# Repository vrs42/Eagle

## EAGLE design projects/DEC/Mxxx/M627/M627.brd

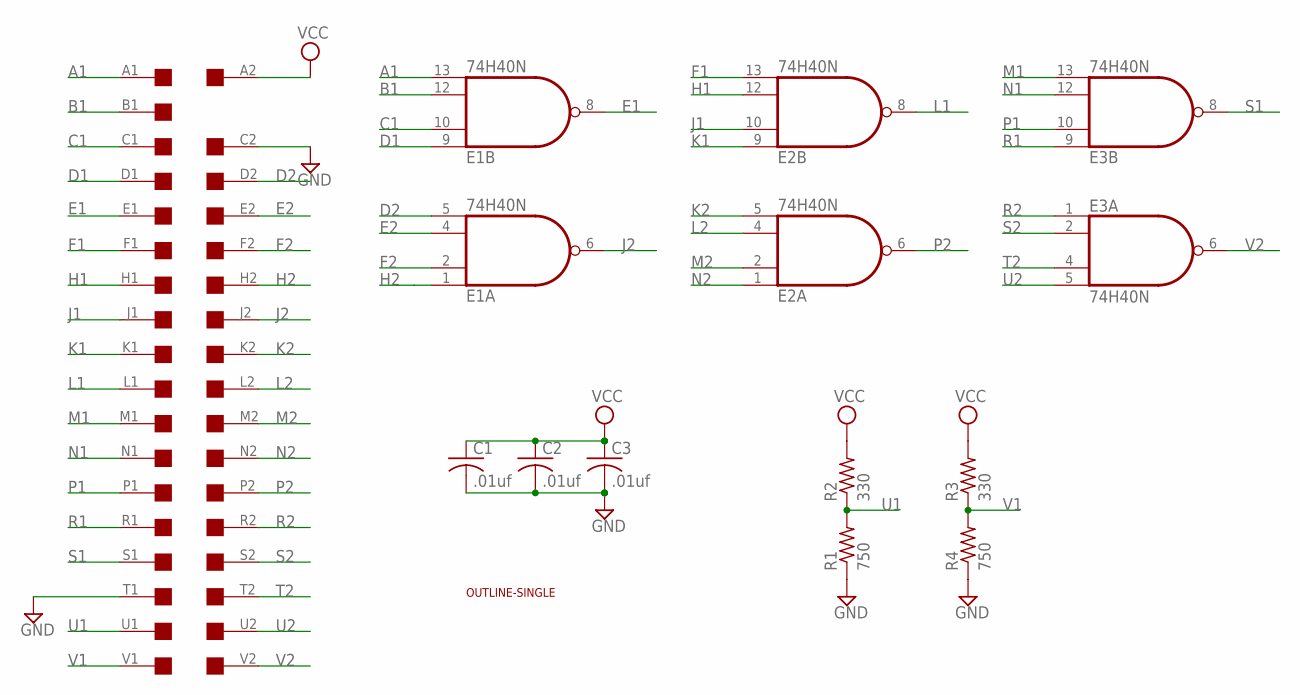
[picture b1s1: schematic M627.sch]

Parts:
C1, C2, C3: .01uf; C050-025X075
E1, E2, E3: 74H40N; DIL14
R1, R4: 750; 0207/10
R2, R3: 330; 0207/10
U$1: OUTLINE-SINGLE; SINGLE
U$2: SINGLE; EDGE-CON2

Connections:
A1: E1.13 (I3), U$2.A1
B1: E1.12 (I2), U$2.B1
C1: E1.10 (I1), U$2.C1
D1: E1.9 (I0), U$2.D1
D2: E1.5 (I3), U$2.D2
E1: E1.8 (O), U$2.E1
E2: E1.4 (I2), U$2.E2
F1: E2.13 (I3), U$2.F1
F2: E1.2 (I1), U$2.F2
GND: C1.2, C2.2, C3.2, E1.7 (GND), E2.7 (GND), E3.7 (GND), R1.1, R4.1, U$2.C2, U$2.T1
H1: E2.12 (I2), U$2.H1
H2: E1.1 (I0), U$2.H2
J1: E2.10 (I1), U$2.J1
J2: E1.6 (O), U$2.J2
K1: E2.9 (I0), U$2.K1
K2: E2.5 (I3), U$2.K2
L1: E2.8 (O), U$2.L1
L2: E2.4 (I2), U$2.L2
M1: E3.13 (I3), U$2.M1
M2: E2.2 (I1), U$2.M2
N1: E3.12 (I2), U$2.N1
N2: E2.1 (I0), U$2.N2
P1: E3.10 (I1), U$2.P1
P2: E2.6 (O), U$2.P2
R1: E3.9 (I0), U$2.R1
R2: E3.1 (I0), U$2.R2
S1: E3.8 (O), U$2.S1
S2: E3.2 (I1), U$2.S2
T2: E3.4 (I2), U$2.T2
U1: R1.2, R2.1, U$2.U1
U2: E3.5 (I3), U$2.U2
V1: R3.1, R4.2, U$2.V1
V2: E3.6 (O), U$2.V2
VCC: C1.1, C2.1, C3.1, E1.14 (VCC), E2.14 (VCC), E3.14 (VCC), R2.2, R3.2, U$2.A2

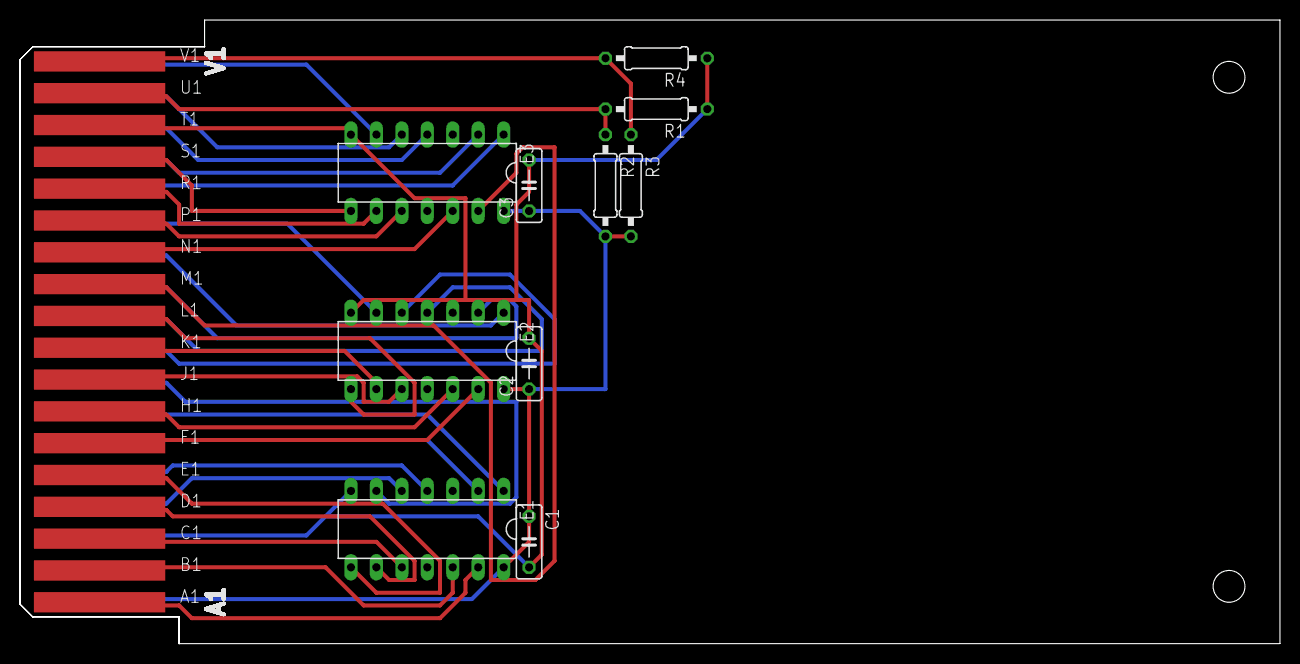
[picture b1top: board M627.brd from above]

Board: 2 copper layers, 125.7 x 62.2 mm, 12 parts (0 on the bottom side), 34 nets.

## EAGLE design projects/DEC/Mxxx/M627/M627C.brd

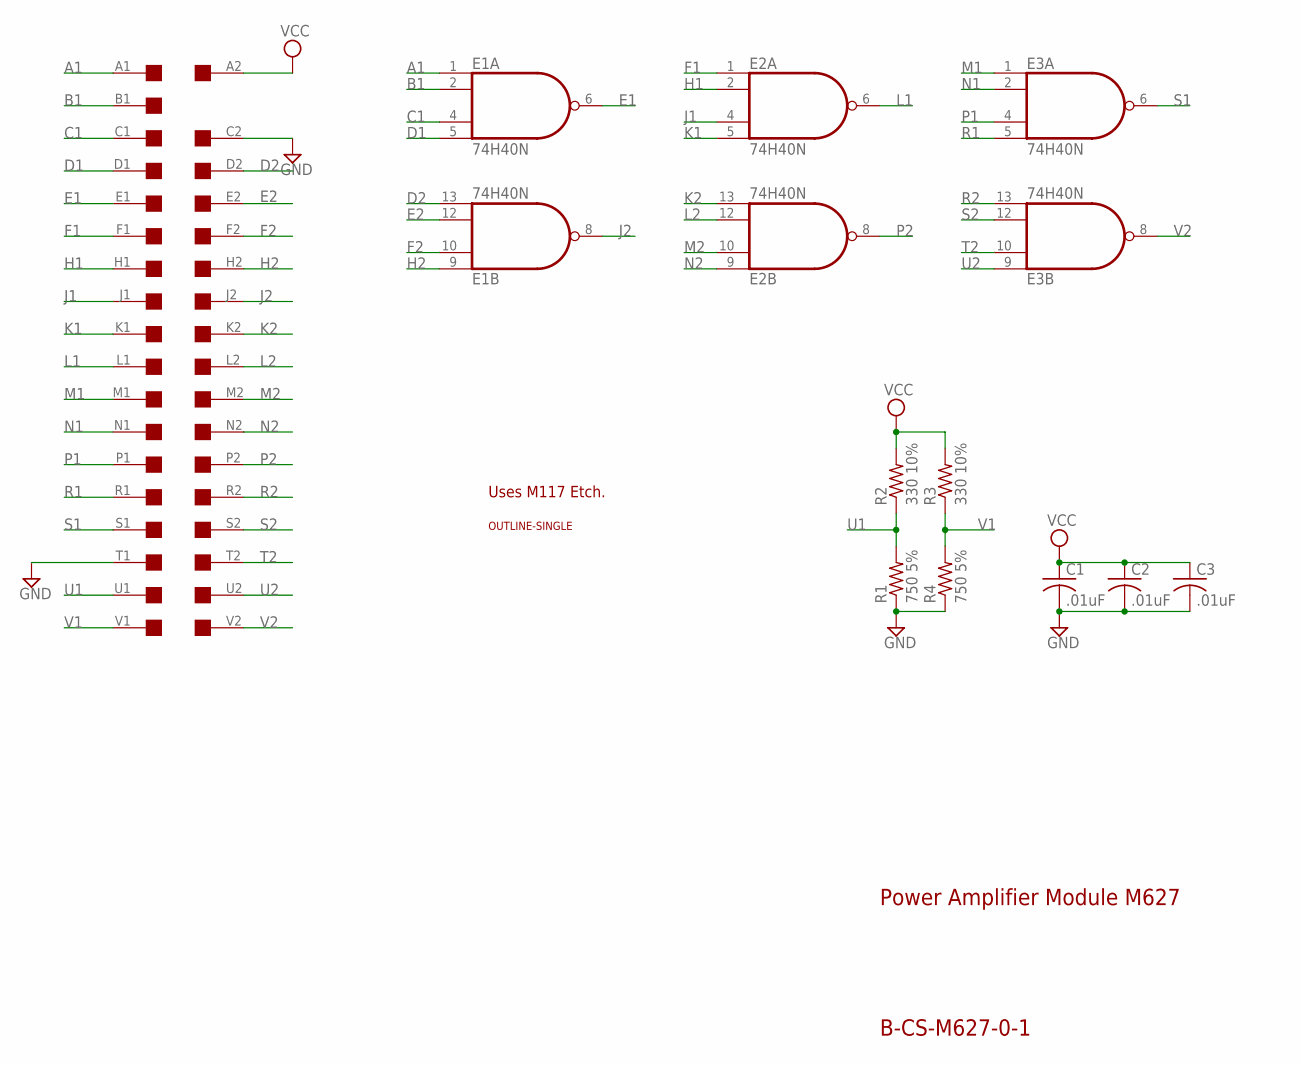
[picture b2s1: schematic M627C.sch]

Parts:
C1, C2, C3: .01uF; C050-025X075
E1, E2, E3: 74H40N; DIL14
R1, R4: 750 5%; 0207/10
R2, R3: 330 10%; 0207/10
U$1: SINGLE; EDGE-CON2
U$4: OUTLINE-SINGLE; SINGLE

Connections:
A1: E1.1 (I0), U$1.A1
B1: E1.2 (I1), U$1.B1
C1: E1.4 (I2), U$1.C1
D1: E1.5 (I3), U$1.D1
D2: E1.13 (I3), U$1.D2
E1: E1.6 (O), U$1.E1
E2: E1.12 (I2), U$1.E2
F1: E2.1 (I0), U$1.F1
F2: E1.10 (I1), U$1.F2
GND: C1.2, C2.2, C3.2, E1.7 (GND), E2.7 (GND), E3.7 (GND), R1.1, R4.1, U$1.C2, U$1.T1
H1: E2.2 (I1), U$1.H1
H2: E1.9 (I0), U$1.H2
J1: E2.4 (I2), U$1.J1
J2: E1.8 (O), U$1.J2
K1: E2.5 (I3), U$1.K1
K2: E2.13 (I3), U$1.K2
L1: E2.6 (O), U$1.L1
L2: E2.12 (I2), U$1.L2
M1: E3.1 (I0), U$1.M1
M2: E2.10 (I1), U$1.M2
N1: E3.2 (I1), U$1.N1
N2: E2.9 (I0), U$1.N2
P1: E3.4 (I2), U$1.P1
P2: E2.8 (O), U$1.P2
R1: E3.5 (I3), U$1.R1
R2: E3.13 (I3), U$1.R2
S1: E3.6 (O), U$1.S1
S2: E3.12 (I2), U$1.S2
T2: E3.10 (I1), U$1.T2
U1: R1.2, R2.1, U$1.U1
U2: E3.9 (I0), U$1.U2
V1: R3.1, R4.2, U$1.V1
V2: E3.8 (O), U$1.V2
VCC: C1.1, C2.1, C3.1, E1.14 (VCC), E2.14 (VCC), E3.14 (VCC), R2.2, R3.2, U$1.A2

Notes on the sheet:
Power Amplifier Module M627
B-CS-M627-0-1
Uses M117 Etch.

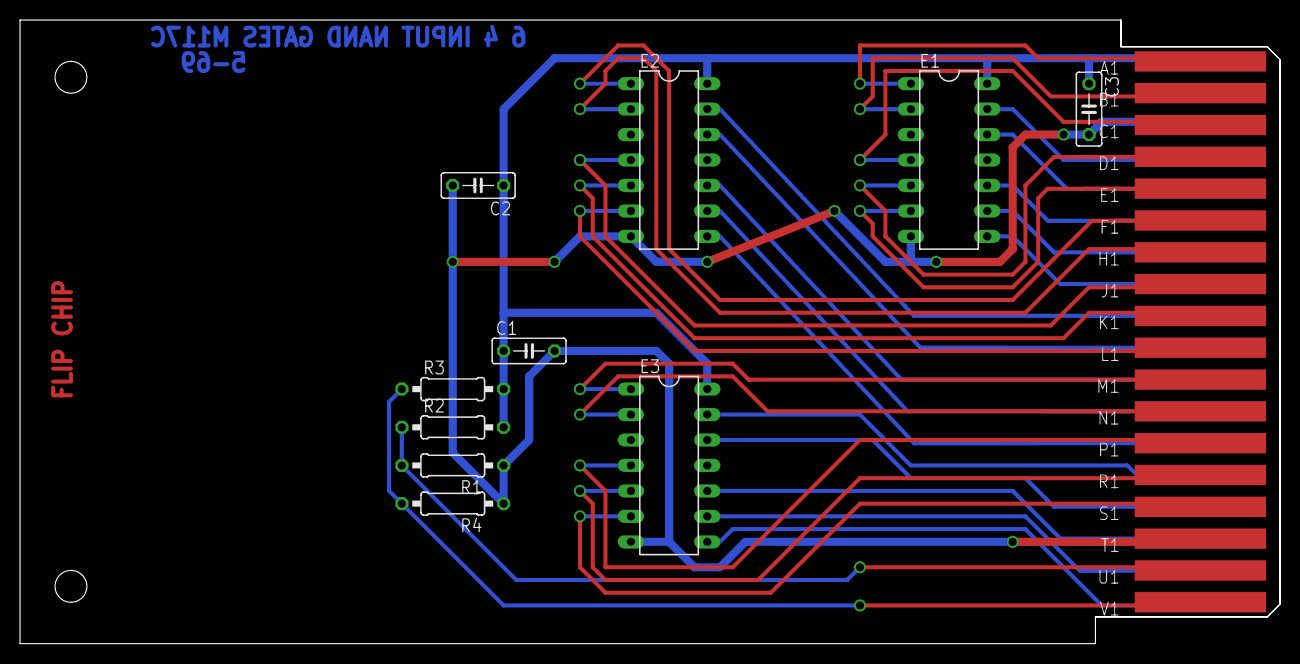
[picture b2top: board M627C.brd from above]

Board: 2 copper layers, 125.7 x 62.2 mm, 12 parts (0 on the bottom side), 34 nets.

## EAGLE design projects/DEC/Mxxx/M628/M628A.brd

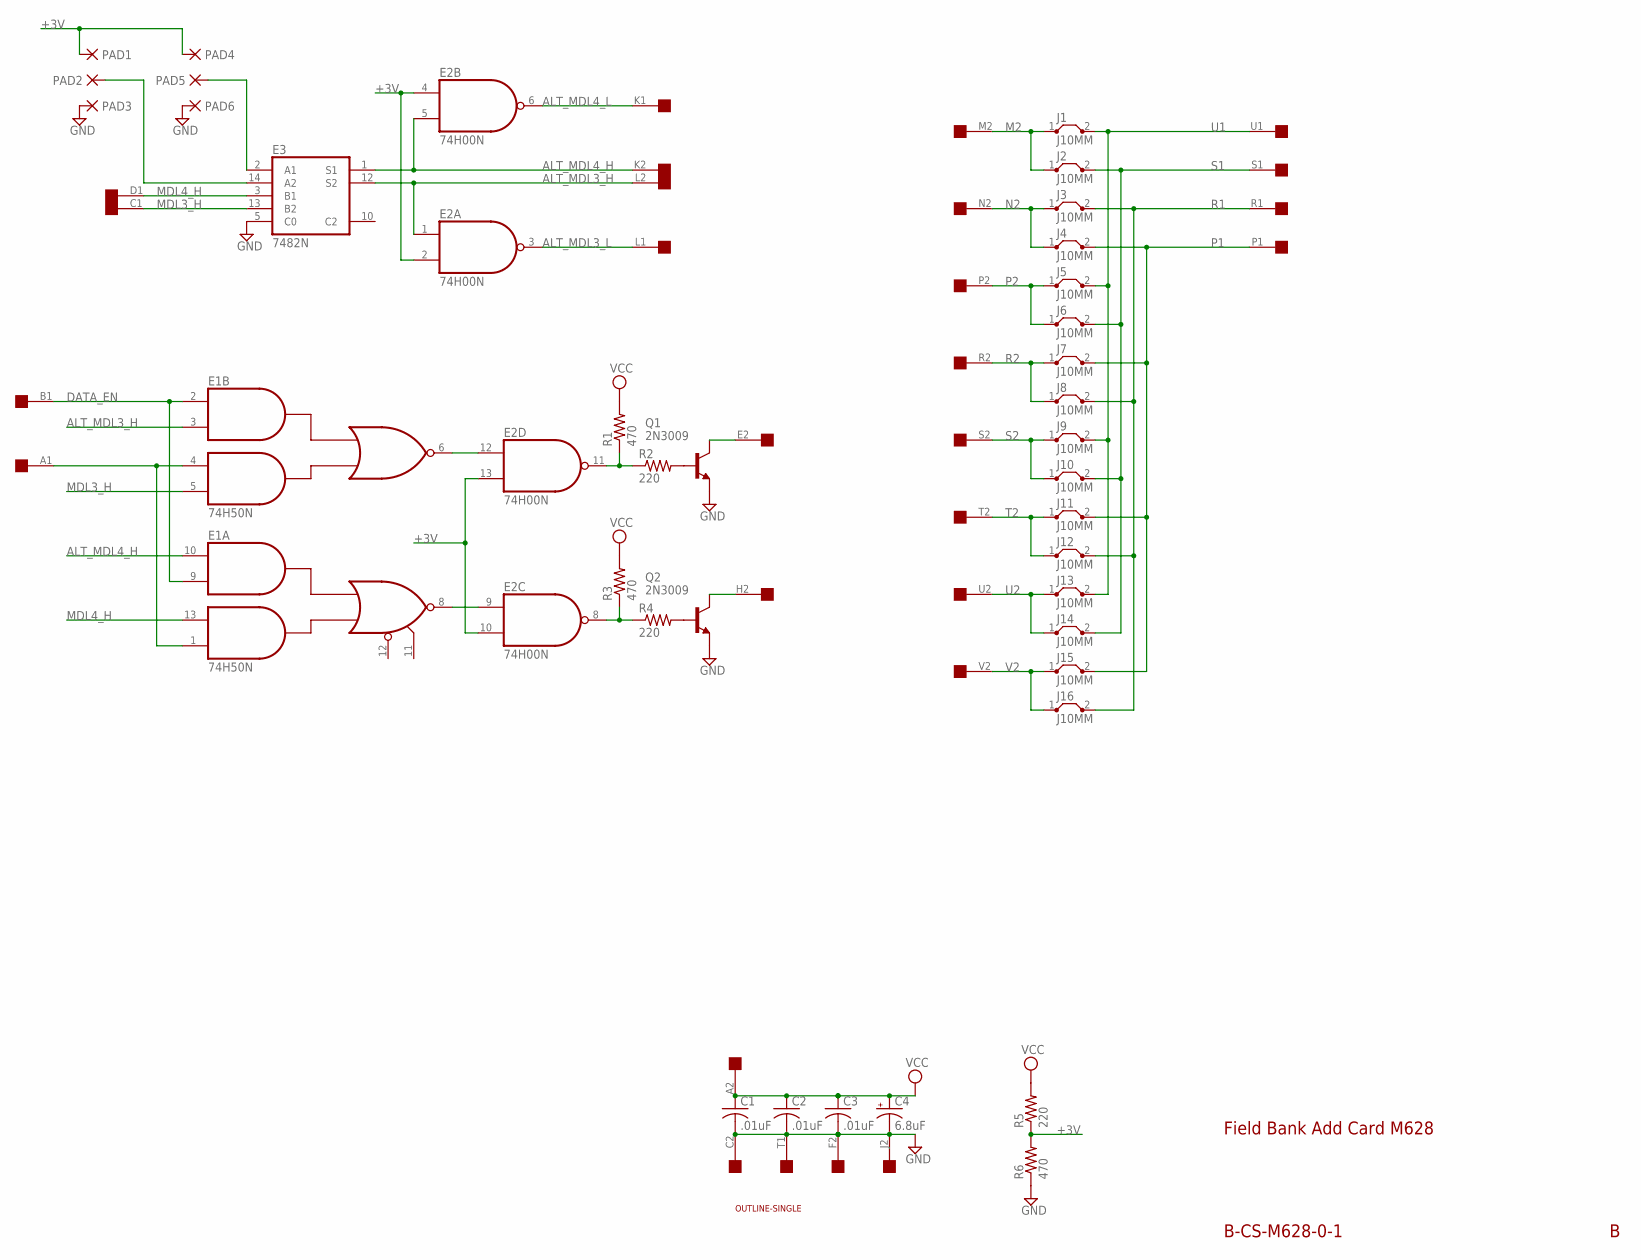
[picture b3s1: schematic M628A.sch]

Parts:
C1, C2, C3: .01uF; C050-025X075
C4: 6.8uF; E12-8
E1: 74H50N; DIL14
E2: 74H00N; DIL14
E3: 7482N; DIL14
J1, J2, J3, J4, J5, J6, J7, J8, J9, J10, J11, J12, J13, J14, J15, J16: J10MM; 10
PAD1, PAD2, PAD3, PAD4, PAD5, PAD6: PAD-0420; 0420
Q1, Q2: 2N3009; TO5
R1, R3, R6: 470; 0207/10
R2, R4, R5: 220; 0207/10
U$1: OUTLINE-SINGLE; SINGLE
U$2: SINGLE; EDGE-CON2

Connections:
+3V: E2.2 (I1), E2.4 (I0), E2.10 (I1), E2.13 (I1), PAD1.P$1, PAD4.P$1, R5.1, R6.2
ALT_MDL3_H: E1.3 (I2), E2.1 (I0), E3.12 (S2), U$2.L2
ALT_MDL3_L: E2.3 (O), U$2.L1
ALT_MDL4_H: E1.10 (I1), E2.5 (I1), E3.1 (S1), U$2.K2
ALT_MDL4_L: E2.6 (O), U$2.K1
DATA_EN: E1.2 (I1), E1.9 (I2), U$2.B1
GND: C1.2, C2.2, C3.2, C4.-, E1.7 (GND), E2.7 (GND), E3.5 (C0), E3.11 (GND), PAD3.P$1, PAD6.P$1, Q1.1 (E), Q2.1 (E), R6.1, U$2.C2, U$2.F2, U$2.J2, U$2.T1
M2: J1.1, J2.1, U$2.M2
MDL3_H: E1.5 (I4), E3.13 (B2), U$2.C1
MDL4_H: E1.13 (I3), E3.3 (B1), U$2.D1
N2: J3.1, J4.1, U$2.N2
unnamed: E3.2 (A1), PAD5.P$1
unnamed: E3.14 (A2), PAD2.P$1
unnamed: E1.8 (O), E2.9 (I0)
unnamed: E1.1 (I4), E1.4 (I3), U$2.A1
unnamed: E1.6 (O), E2.12 (I0)
unnamed: E2.11 (O), R1.1, R2.1
unnamed: E2.8 (O), R3.1, R4.1
unnamed: Q1.2 (B), R2.2
unnamed: Q2.2 (B), R4.2
unnamed: Q1.3 (C), U$2.E2
unnamed: Q2.3 (C), U$2.H2
P1: J4.2, J7.2, J11.2, J15.2, U$2.P1
P2: J5.1, J6.1, U$2.P2
R1: J3.2, J8.2, J12.2, J16.2, U$2.R1
R2: J7.1, J8.1, U$2.R2
S1: J2.2, J6.2, J10.2, J14.2, U$2.S1
S2: J9.1, J10.1, U$2.S2
T2: J11.1, J12.1, U$2.T2
U1: J1.2, J5.2, J9.2, J13.2, U$2.U1
U2: J13.1, J14.1, U$2.U2
V2: J15.1, J16.1, U$2.V2
VCC: C1.1, C2.1, C3.1, C4.+, E1.14 (VCC), E2.14 (VCC), E3.4 (VCC), R1.2, R3.2, R5.2, U$2.A2

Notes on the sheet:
Field Bank Add Card M628
B-CS-M628-0-1

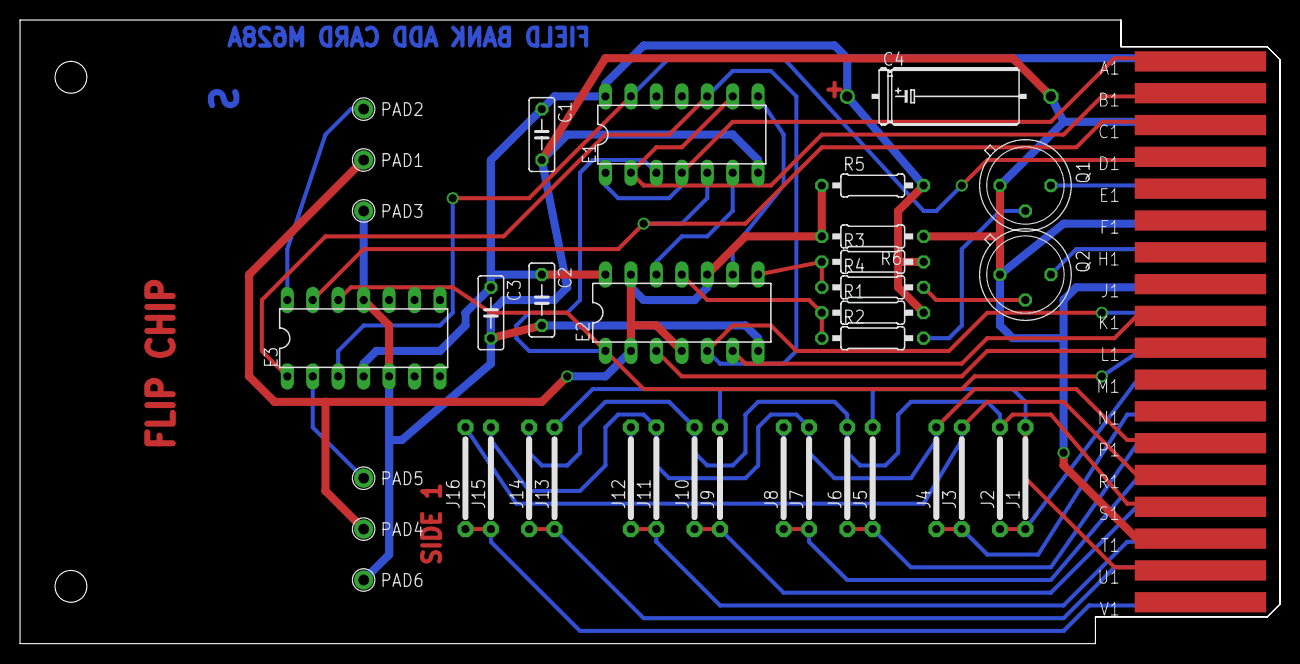
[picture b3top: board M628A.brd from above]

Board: 2 copper layers, 125.7 x 62.2 mm, 40 parts (0 on the bottom side), 33 nets.

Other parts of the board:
U$3: FLIPCHIP

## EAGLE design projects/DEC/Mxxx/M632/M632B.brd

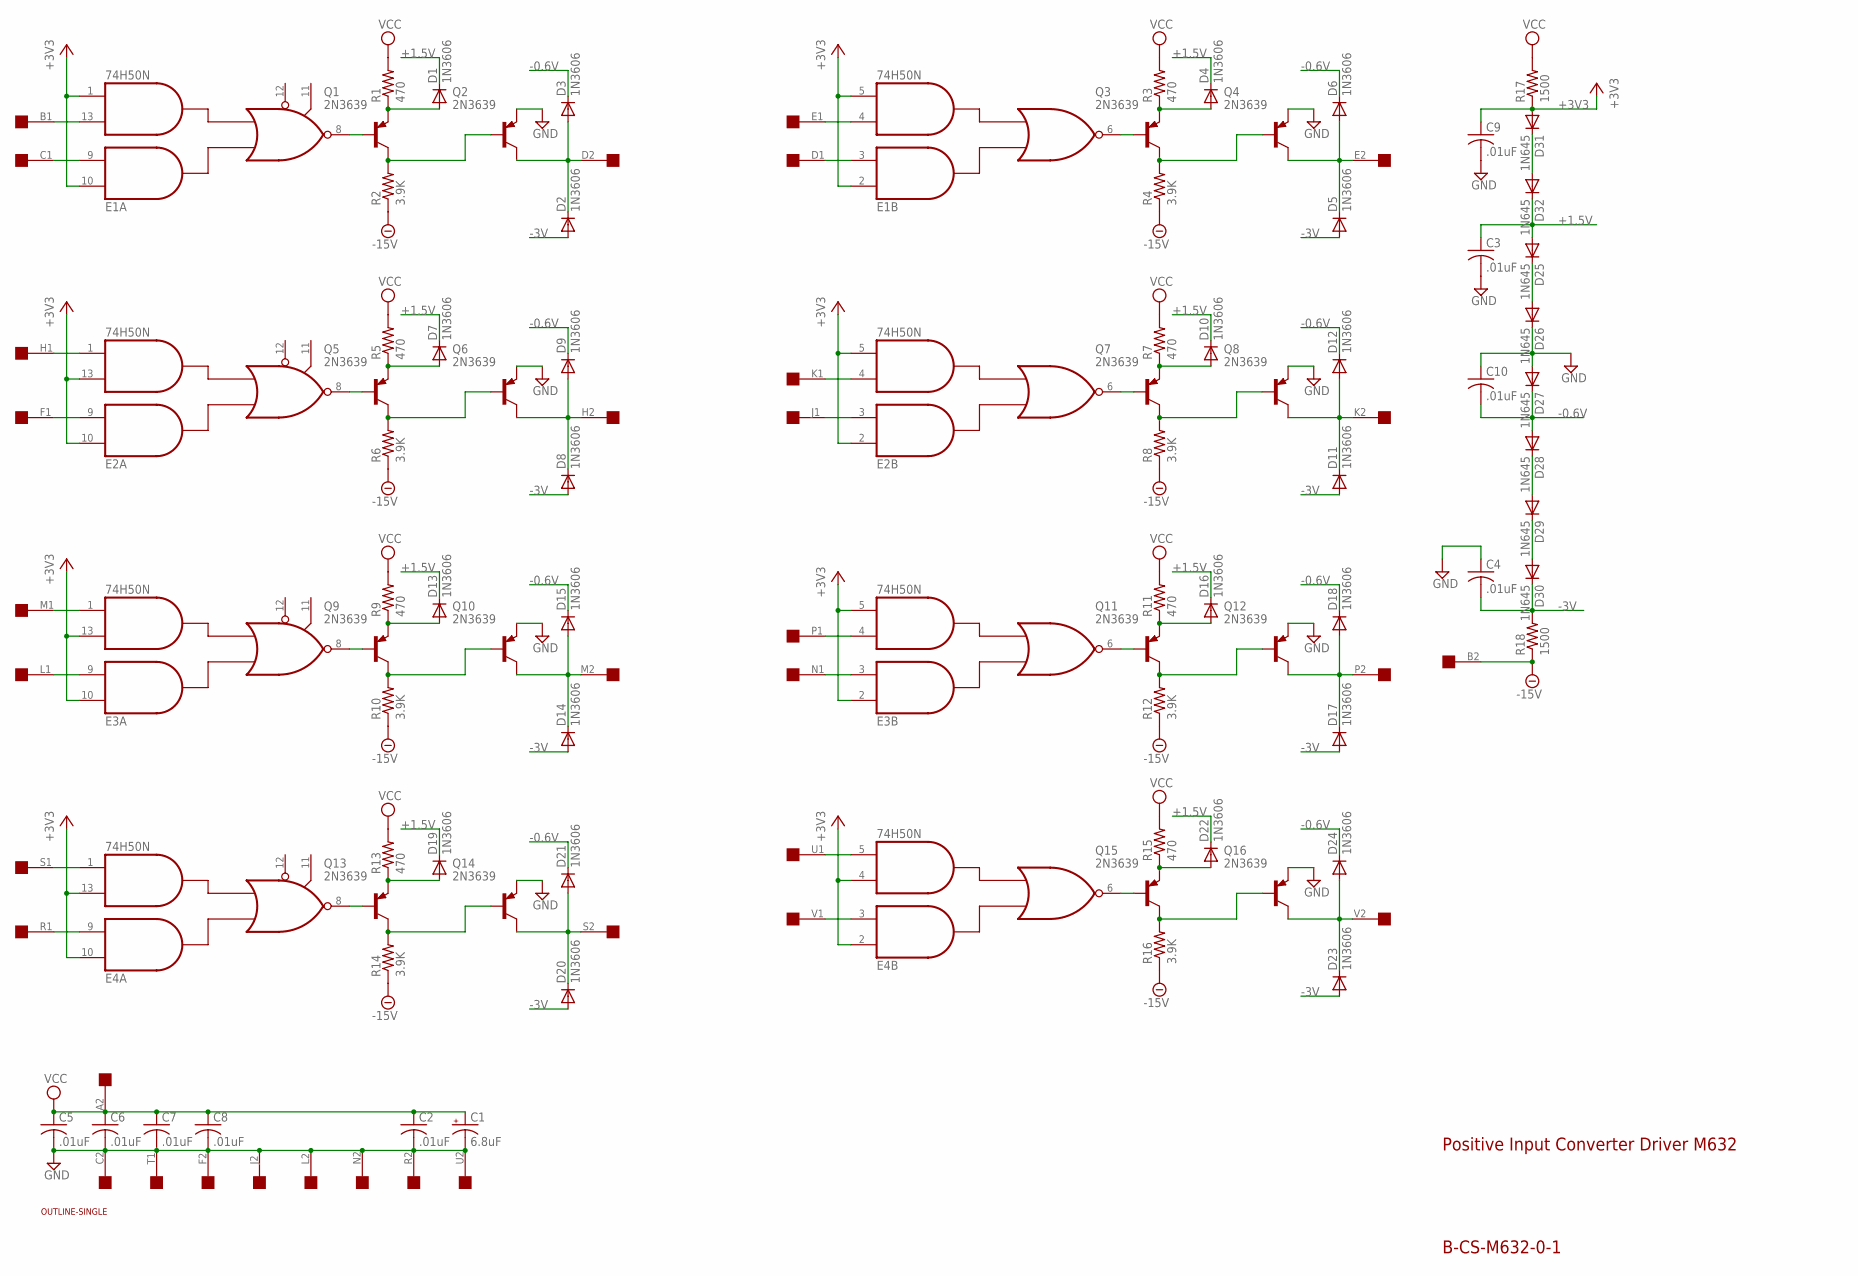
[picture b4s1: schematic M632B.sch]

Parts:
C1: 6.8uF; E12-8
C2, C3, C4, C5, C6, C7, C8, C9, C10: .01uF; C050-025X075
D1, D2, D3, D4, D5, D6, D7, D8, D9, D10, D11, D12, D13, D14, D15, D16, D17, D18, D19, D20, D21, D22, D23, D24: 1N3606; DO35-10
D25, D26, D27, D28, D29, D30, D31, D32: 1N645; DO35-10
E1, E2, E3, E4: 74H50N; DIL14
Q1, Q2, Q3, Q4, Q5, Q6, Q7, Q8, Q9, Q10, Q11, Q12, Q13, Q14, Q15, Q16: 2N3639; TO39
R1, R3, R5, R7, R9, R11, R13, R15: 470; 0207/10
R2, R4, R6, R8, R10, R12, R14, R16: 3.9K; 0207/10
R17, R18: 1500; 0207/10
U$1: SINGLE; EDGE-CON2
U$4: OUTLINE-SINGLE; SINGLE

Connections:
+1.5V: C3.1, D1.C, D4.C, D7.C, D10.C, D13.C, D16.C, D19.C, D22.C, D25.A, D32.C
+3V3: C9.1, D31.A, E1.1 (I4), E1.2 (I1), E1.5 (I4), E1.10 (I1), E2.2 (I1), E2.5 (I4), E2.10 (I1), E2.13 (I3), E3.2 (I1), E3.5 (I4), E3.10 (I1), E3.13 (I3), E4.2 (I1), E4.4 (I3), E4.10 (I1), E4.13 (I3), R17.1
-0.6V: C10.2, D3.C, D6.C, D9.C, D12.C, D15.C, D18.C, D21.C, D24.C, D27.C, D28.A
-3V: C4.2, D2.A, D5.A, D8.A, D11.A, D14.A, D17.A, D20.A, D23.A, D30.C, R18.2
-15V: R2.1, R4.1, R6.1, R8.1, R10.1, R12.1, R14.1, R16.1, R18.1, U$1.B2
GND: C1.-, C2.2, C3.2, C4.1, C5.2, C6.2, C7.2, C8.2, C9.2, C10.1, D26.C, D27.A, E1.7 (GND), E2.7 (GND), E3.7 (GND), E4.7 (GND), Q2.1 (E), Q4.1 (E), Q6.1 (E), Q8.1 (E), Q10.1 (E), Q12.1 (E), Q14.1 (E), Q16.1 (E), U$1.C2, U$1.F2, U$1.J2, U$1.L2, U$1.N2, U$1.R2, U$1.T1, U$1.U2
unnamed: E2.3 (I2), U$1.J1
unnamed: E2.4 (I3), U$1.K1
unnamed: E1.9 (I2), U$1.C1
unnamed: E1.13 (I3), U$1.B1
unnamed: E4.1 (I4), U$1.S1
unnamed: E4.9 (I2), U$1.R1
unnamed: E1.8 (O), Q1.2 (B)
unnamed: Q1.3 (C), Q2.2 (B), R2.2
unnamed: E2.8 (O), Q5.2 (B)
unnamed: D7.A, Q5.1 (E), R5.1
unnamed: D2.C, D3.A, Q2.3 (C), U$1.D2
unnamed: Q5.3 (C), Q6.2 (B), R6.2
unnamed: D8.C, D9.A, Q6.3 (C), U$1.H2
unnamed: E4.3 (I2), U$1.V1
unnamed: E4.5 (I4), U$1.U1
unnamed: E3.1 (I4), U$1.M1
unnamed: E3.9 (I2), U$1.L1
unnamed: E3.8 (O), Q9.2 (B)
unnamed: D13.A, Q9.1 (E), R9.1
unnamed: Q9.3 (C), Q10.2 (B), R10.2
unnamed: D14.C, D15.A, Q10.3 (C), U$1.M2
unnamed: E4.8 (O), Q13.2 (B)
unnamed: D19.A, Q13.1 (E), R13.1
unnamed: Q13.3 (C), Q14.2 (B), R14.2
unnamed: D20.C, D21.A, Q14.3 (C), U$1.S2
unnamed: E1.6 (O), Q3.2 (B)
unnamed: D4.A, Q3.1 (E), R3.1
unnamed: Q3.3 (C), Q4.2 (B), R4.2
unnamed: E1.4 (I3), U$1.E1
unnamed: E1.3 (I2), U$1.D1
unnamed: D5.C, D6.A, Q4.3 (C), U$1.E2
unnamed: E2.6 (O), Q7.2 (B)
unnamed: E2.1 (I4), U$1.H1
unnamed: E3.3 (I2), U$1.N1
unnamed: E3.4 (I3), U$1.P1
unnamed: E2.9 (I2), U$1.F1
unnamed: D10.A, Q7.1 (E), R7.1
unnamed: Q7.3 (C), Q8.2 (B), R8.2
unnamed: D11.C, D12.A, Q8.3 (C), U$1.K2
unnamed: E3.6 (O), Q11.2 (B)
unnamed: D1.A, Q1.1 (E), R1.1
unnamed: D16.A, Q11.1 (E), R11.1
unnamed: Q11.3 (C), Q12.2 (B), R12.2
unnamed: D17.C, D18.A, Q12.3 (C), U$1.P2
unnamed: E4.6 (O), Q15.2 (B)
unnamed: D22.A, Q15.1 (E), R15.1
unnamed: Q15.3 (C), Q16.2 (B), R16.2
unnamed: D23.C, D24.A, Q16.3 (C), U$1.V2
unnamed: D25.C, D26.A
unnamed: D28.C, D29.A
unnamed: D31.C, D32.A
unnamed: D29.C, D30.A
VCC: C1.+, C2.1, C5.1, C6.1, C7.1, C8.1, E1.14 (VCC), E2.14 (VCC), E3.14 (VCC), E4.14 (VCC), R1.2, R3.2, R5.2, R7.2, R9.2, R11.2, R13.2, R15.2, R17.2, U$1.A2

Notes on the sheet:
Positive Input Converter Driver M632
B-CS-M632-0-1

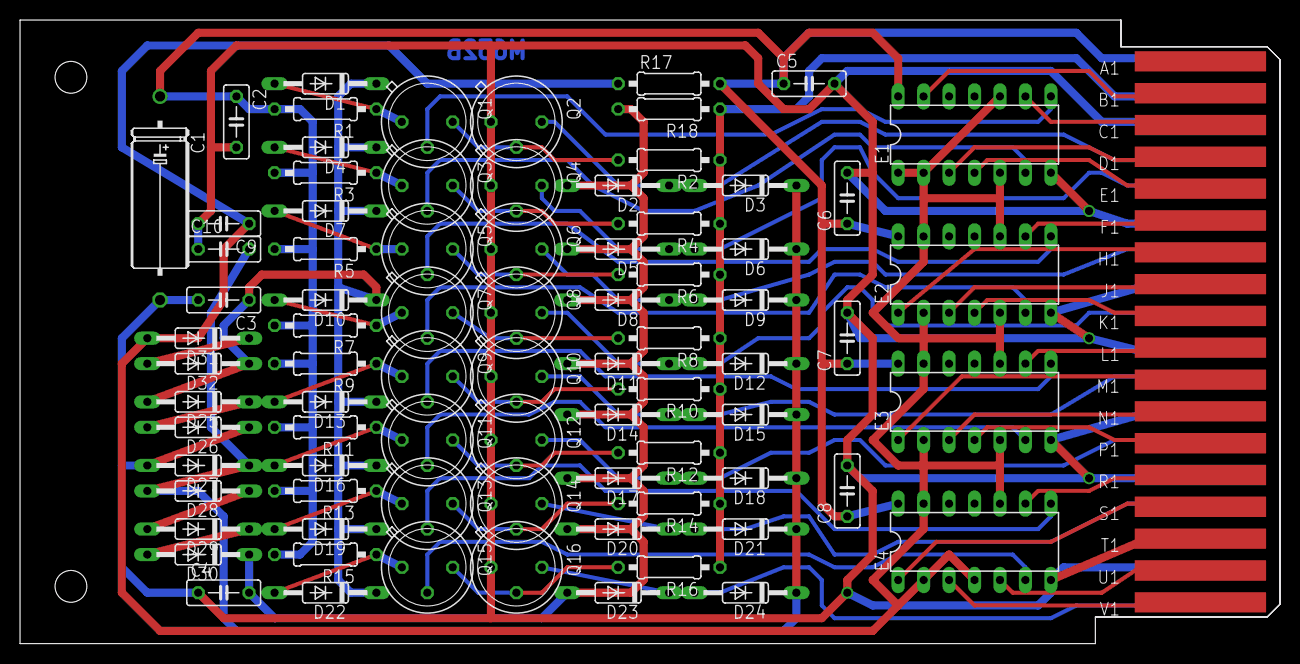
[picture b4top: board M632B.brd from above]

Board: 2 copper layers, 125.7 x 62.2 mm, 82 parts (0 on the bottom side), 59 nets.
